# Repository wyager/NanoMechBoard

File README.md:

# NanoMechBoard
This project is the teensy code for Will Yager's even smaller custom mechanical keyboard
project.

The code serves two functions:

1. If plugged into USB, the device will act as a stand-alone keyboard with 33
keys. ("The master")
2. If a second device is plugged into that first device, the two devices will
share relevant information over I2C. In this way, two of these devices can be
connected to form a 66-key keyboard. With some modification to the firmware and
the I2C pull-up resistors, one could theoretically chain up to 129 boards
together (I believe).

## Building/installing
1. Install `avr-gcc`.
2. Install Teensy loader.
3. `cd src`
4. `make`
5. Drag `main.hex` into Teensy loader.
6. Program Teensy.

## Modifying key layout
1. Modify `keys[]` in `KeyMapper.cpp`.
2. Replace values like `KEY_A` with other values from `keylayouts.h`.

This should be fairly simple to figure out. Within the file, I have `keys[]`
laid out just like the physical keys.

## Program structure

### main.cpp

```
       Start USB/I2C
       Determine master/slave status
       
       forever:
              led_status
              => get hardware state from HardwareController
              => debounce buttons with ButtonDebouncer
              => detect changes in buttons with ButtonDeltaDetector
              => map button changes to key changes with KeyMapper
              =: key_changes

              led_status
              => update the slave (if it exists) with the SlaveNotifier
              =: slave_key_changes

              key_changes, slave_key_changes
              => notify the master (over USB or I2C) of key changes with the MasterNotifier
              =: led_status

```

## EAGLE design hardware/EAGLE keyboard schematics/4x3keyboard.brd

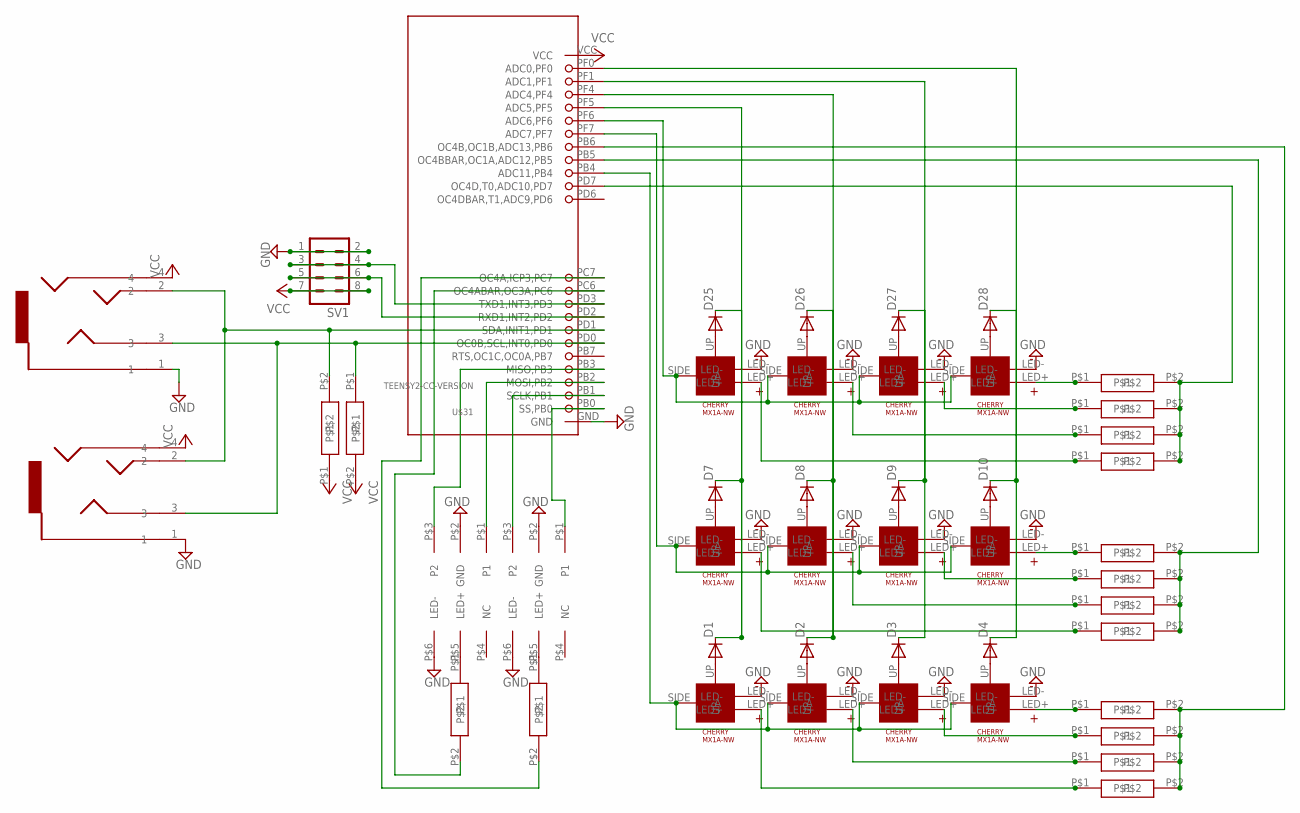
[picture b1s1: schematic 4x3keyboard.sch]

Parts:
COMM, COMM1: SJ-43514_HEADPHONES_3.5MM_X4; SJ-43514_HEADPHONES-3.5MM_X4
D1, D2, D3, D4, D7, D8, D9, D10, D25, D26, D27, D28: 1N4148DO35-7; DO35-7
SV1: MA04-2
U$1, U$2, U$3, U$4, U$7, U$8, U$9, U$10, U$25, U$26, U$27, U$28: CHERRY-MX1A-E1NW-LED; CHERRYMX-NN-LED
U$5, U$6, U$11, U$12, U$13, U$14, U$15, U$16, U$17, U$18, U$19, U$20, U$21, U$22, U$29, U$30: RESISTORBIGPAD
U$23, U$24: NKK_GW_SERIES
U$31: TEENSY2-CC-VERSION; TEENSY2

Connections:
GND: COMM.1, COMM1.1, SV1.1, SV1.2, U$1.LED-, U$2.LED-, U$3.LED-, U$4.LED-, U$7.LED-, U$8.LED-, U$9.LED-, U$10.LED-, U$23.P$2 (GND), U$23.P$6 (LED-), U$24.P$2 (GND), U$24.P$6 (LED-), U$25.LED-, U$26.LED-, U$27.LED-, U$28.LED-, U$31.GND
unnamed: D1.A, U$2.UP
unnamed: D2.A, U$1.UP
unnamed: D3.A, U$3.UP
unnamed: D4.A, U$4.UP
unnamed: U$4.LED+, U$12.P$1
unnamed: U$23.P$5 (LED+), U$29.P$1
unnamed: D7.A, U$7.UP
unnamed: D8.A, U$8.UP
unnamed: D9.A, U$9.UP
unnamed: D10.A, U$10.UP
unnamed: U$3.LED+, U$11.P$1
unnamed: U$1.LED+, U$6.P$1
unnamed: U$2.LED+, U$5.P$1
unnamed: U$30.P$2, U$31.PC7 (OC4A,ICP3,PC7)
unnamed: U$24.P$5 (LED+), U$30.P$1
unnamed: COMM.2, COMM1.2, U$21.P$2, U$31.PD1 (SDA,INIT1,PD1)
unnamed: U$29.P$2, U$31.PC6 (OC4ABAR,OC3A,PC6)
unnamed: U$10.LED+, U$13.P$1
unnamed: U$9.LED+, U$14.P$1
unnamed: U$8.LED+, U$15.P$1
unnamed: U$7.LED+, U$16.P$1
unnamed: U$24.P$1 (P1), U$31.PB0 (SS,PB0)
unnamed: U$17.P$1, U$28.LED+
unnamed: U$18.P$1, U$27.LED+
unnamed: D25.A, U$25.UP
unnamed: D26.A, U$26.UP
unnamed: D27.A, U$27.UP
unnamed: D28.A, U$28.UP
unnamed: U$19.P$1, U$26.LED+
unnamed: U$20.P$1, U$25.LED+
unnamed: D1.C, D7.C, D25.C, U$31.PF5 (ADC5,PF5)
unnamed: D2.C, D8.C, D26.C, U$31.PF4 (ADC4,PF4)
unnamed: D3.C, D9.C, D27.C, U$31.PF1 (ADC1,PF1)
unnamed: D4.C, D10.C, D28.C, U$31.PF0 (ADC0,PF0)
unnamed: U$24.P$3 (P2), U$31.PB1 (SCLK,PB1)
unnamed: U$23.P$1 (P1), U$31.PB2 (MOSI,PB2)
unnamed: SV1.3, SV1.4, U$31.PD3 (TXD1,INT3,PD3)
unnamed: U$1.SIDE (A), U$2.SIDE (A), U$3.SIDE (A), U$4.SIDE (A), U$31.PB4 (ADC11,PB4)
unnamed: U$7.SIDE (A), U$8.SIDE (A), U$9.SIDE (A), U$10.SIDE (A), U$31.PF7 (ADC7,PF7)
unnamed: U$25.SIDE (A), U$26.SIDE (A), U$27.SIDE (A), U$28.SIDE (A), U$31.PF6 (ADC6,PF6)
unnamed: SV1.5, SV1.6, U$31.PD2 (RXD1,INT2,PD2)
unnamed: U$23.P$3 (P2), U$31.PB3 (MISO,PB3)
unnamed: U$5.P$2, U$6.P$2, U$11.P$2, U$12.P$2, U$31.PB6 (OC4B,OC1B,ADC13,PB6)
unnamed: U$13.P$2, U$14.P$2, U$15.P$2, U$16.P$2, U$31.PB5 (OC4BBAR,OC1A,ADC12,PB5)
unnamed: U$17.P$2, U$18.P$2, U$19.P$2, U$20.P$2, U$31.PD7 (OC4D,T0,ADC10,PD7)
unnamed: COMM.3, COMM1.3, U$22.P$1, U$31.PD0 (OC0B,SCL,INT0,PD0)
VCC: COMM.4, COMM1.4, SV1.7, SV1.8, U$21.P$1, U$22.P$2, U$31.VCC

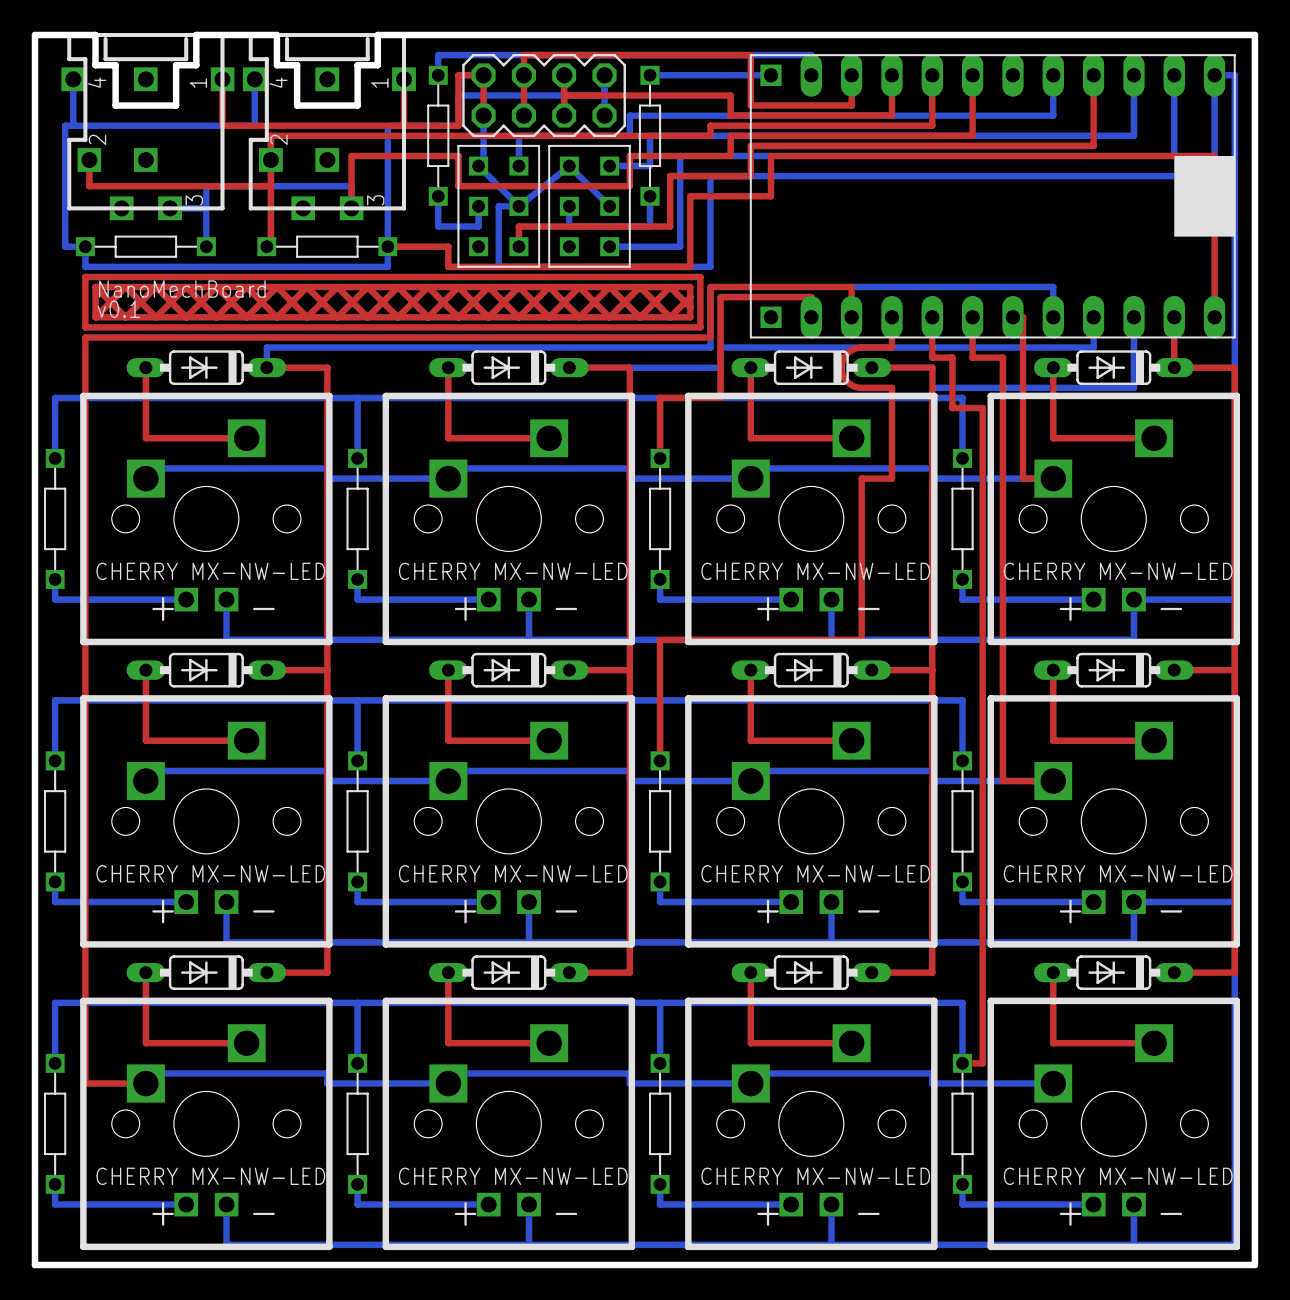
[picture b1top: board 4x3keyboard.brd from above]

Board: 2 copper layers, 76.8 x 77.5 mm, 46 parts (0 on the bottom side), 48 nets.

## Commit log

2015-06-14 work
2015-06-14 newest board
2015-06-14 latest
2015-06-14 new boards
2015-06-27 error fix
2015-07-01 new stuff
2015-07-01 hw test
2015-07-02 added counter
2015-07-04 new files
2015-07-25 lots of progress
2015-07-25 all PWM working
2015-07-26 some work
2015-07-26 working
2015-08-12 mods
